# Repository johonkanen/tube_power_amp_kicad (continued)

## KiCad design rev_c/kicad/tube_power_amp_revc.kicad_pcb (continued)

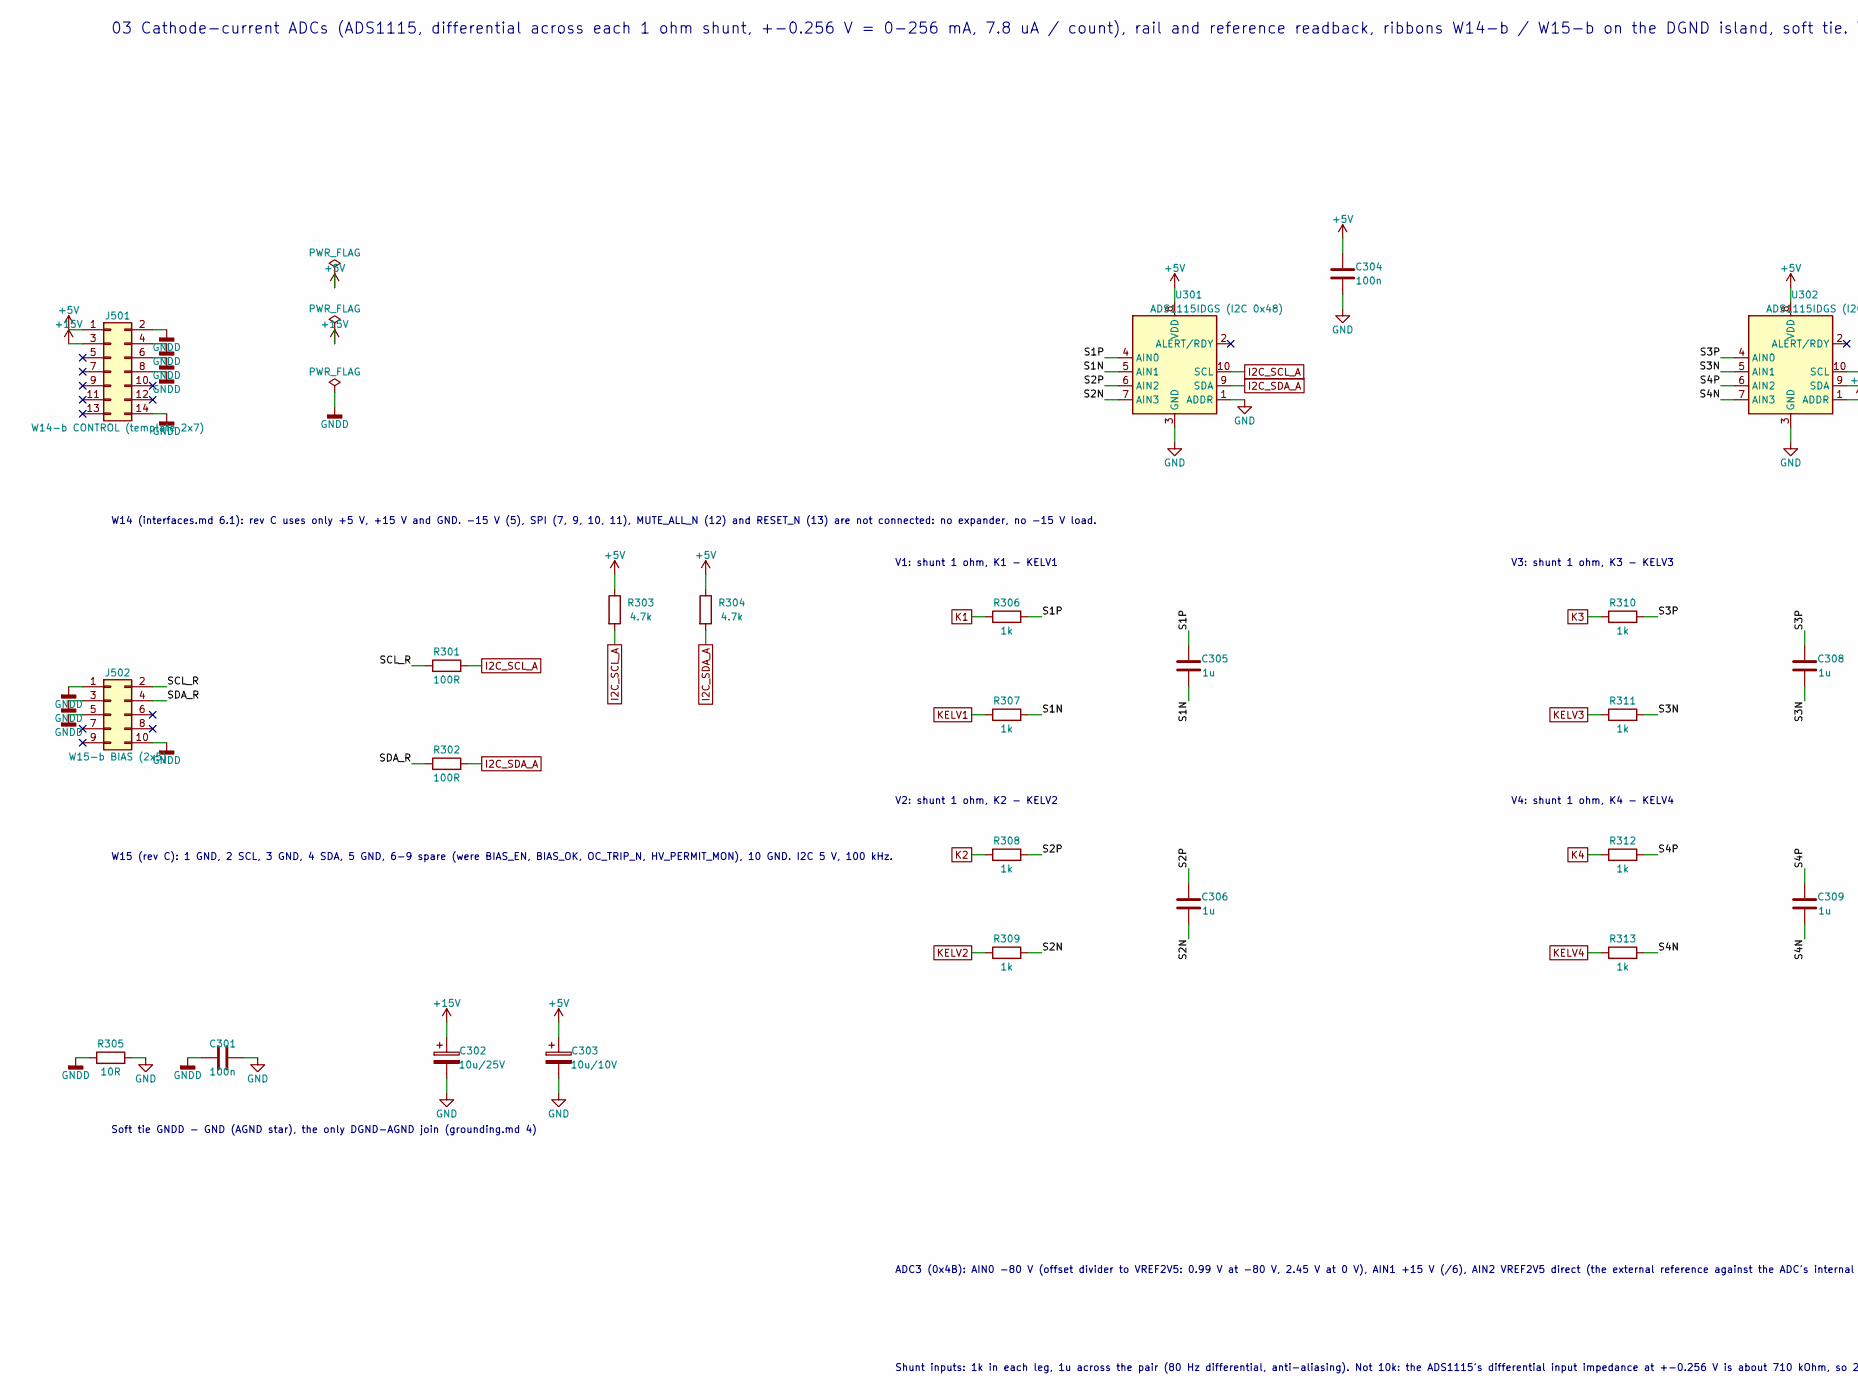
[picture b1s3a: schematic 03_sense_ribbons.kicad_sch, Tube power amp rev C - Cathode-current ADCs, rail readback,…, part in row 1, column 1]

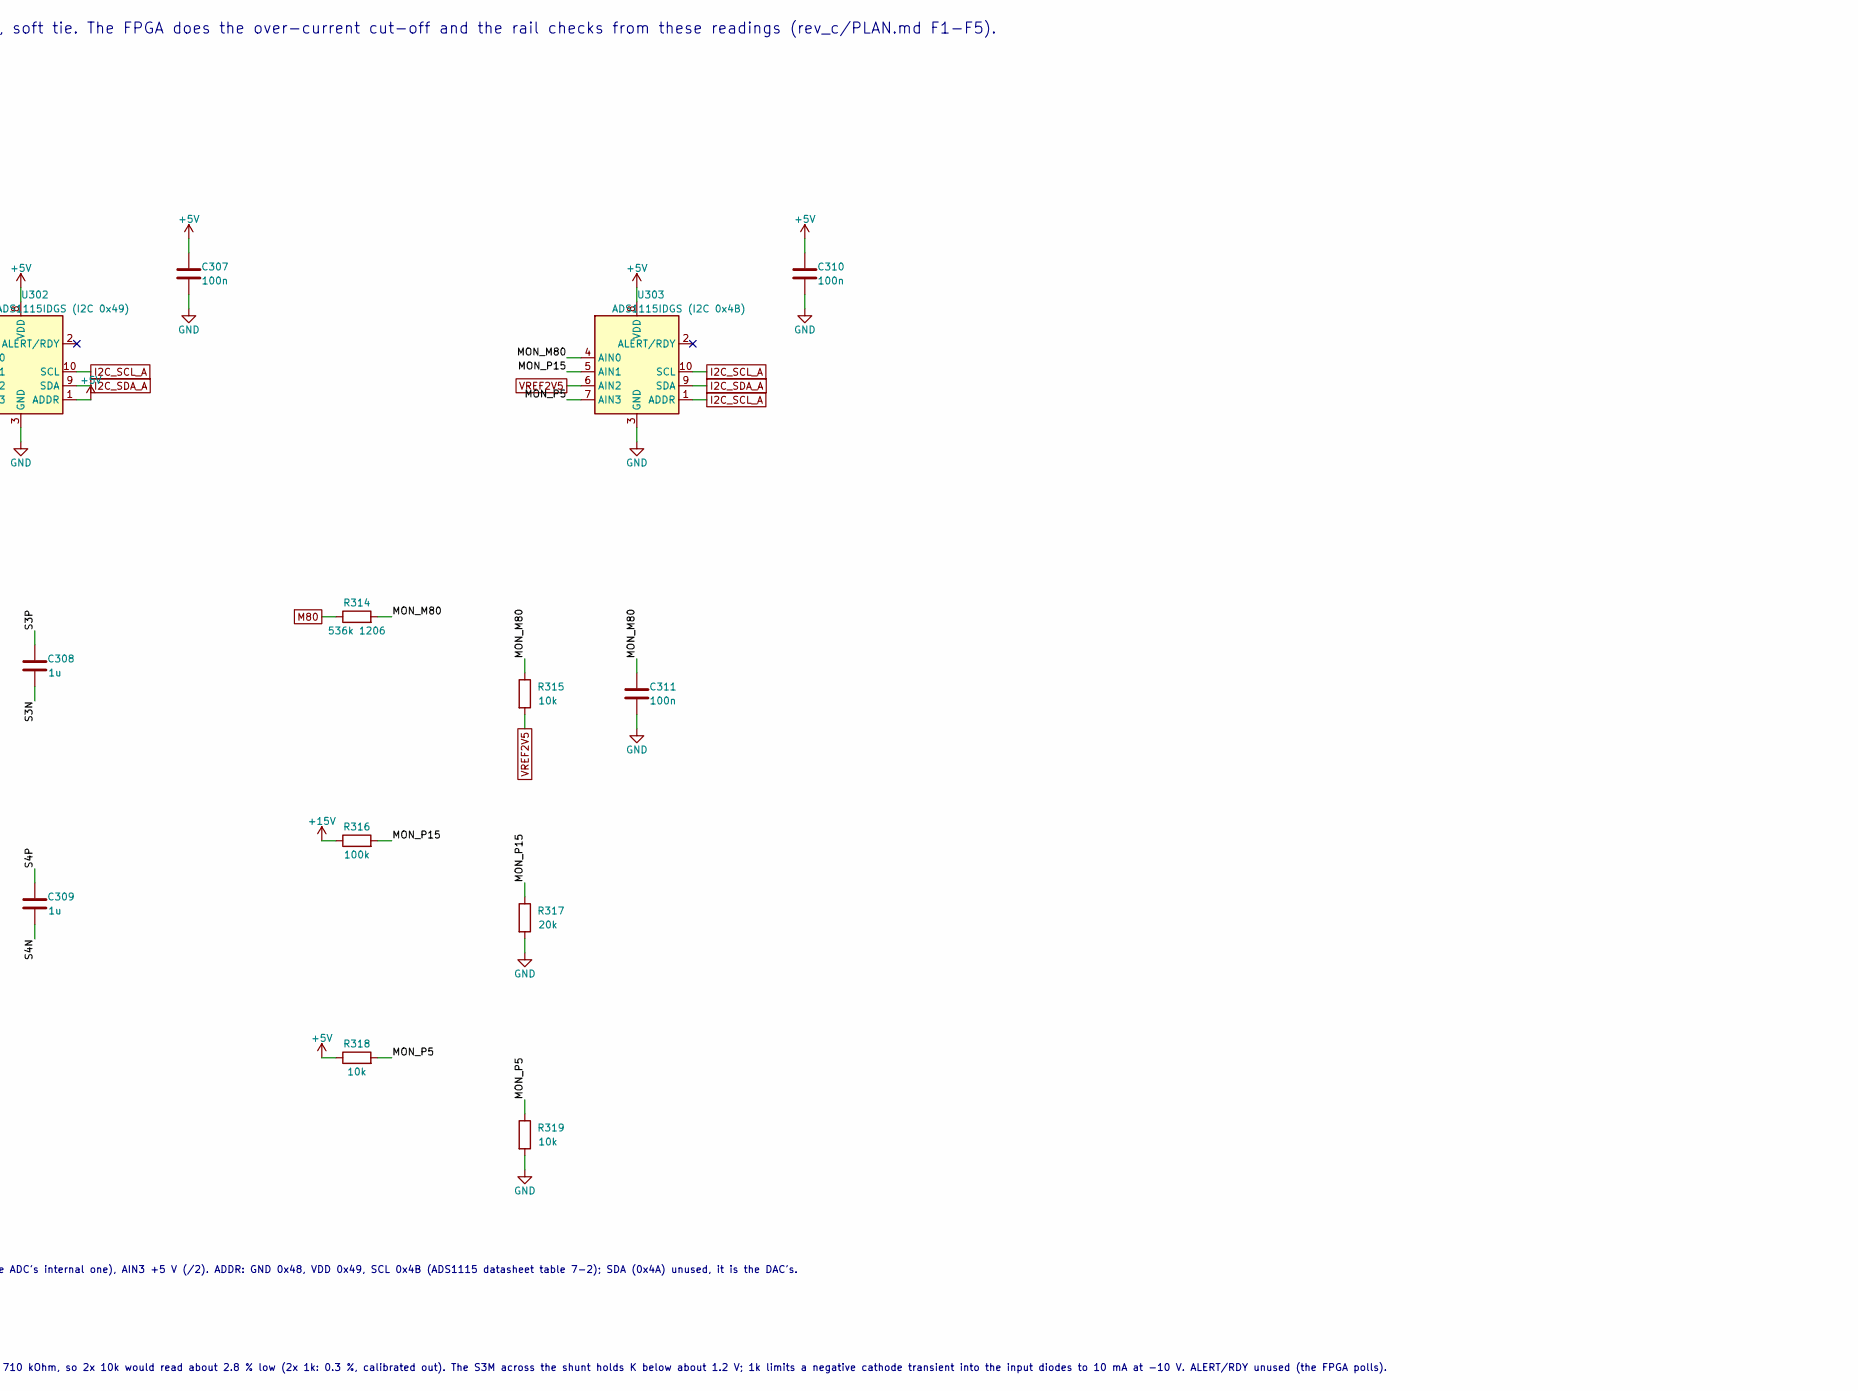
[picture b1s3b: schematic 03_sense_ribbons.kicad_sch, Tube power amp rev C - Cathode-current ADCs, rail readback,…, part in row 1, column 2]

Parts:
C301, C304, C307, C310, C311: 100n; C_0603_1608Metric
C302: 10u/25V; C_1206_3216Metric
C303: 10u/10V; C_1206_3216Metric
C305, C306, C308, C309: 1u; C_0603_1608Metric
J501: W14-b CONTROL (template 2x7); IDC-Header_2x07_P2.54mm_Vertical
J502: W15-b BIAS (2x5); IDC-Header_2x05_P2.54mm_Vertical
R301, R302: 100R; R_0603_1608Metric
R303, R304: 4.7k; R_0603_1608Metric
R305: 10R; R_0603_1608Metric
R306, R307, R308, R309, R310, R311, R312, R313: 1k; R_0603_1608Metric
R314: 536k 1206; R_1206_3216Metric
R315, R318, R319: 10k; R_0603_1608Metric
R316: 100k; R_0603_1608Metric
R317: 20k; R_0603_1608Metric
U301: ADS1115IDGS (I2C 0x48); MSOP-10_3x3mm_P0.5mm
U302: ADS1115IDGS (I2C 0x49); MSOP-10_3x3mm_P0.5mm
U303: ADS1115IDGS (I2C 0x4B); MSOP-10_3x3mm_P0.5mm

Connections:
+5V: C303.1, C304.1, C307.1, C310.1, J501.1, R303.1, R304.1, R318.1, U301.8 (VDD), U302.1 (ADDR), U302.8 (VDD), U303.8 (VDD); also elsewhere on the board
+15V: C302.1, J501.3, R316.1; also elsewhere on the board
/03 Cathode-current ADCs, rail readback, ribbons, DGND island/MON_M80: C311.1, R314.2, R315.1, U303.4 (AIN0)
/03 Cathode-current ADCs, rail readback, ribbons, DGND island/MON_P5: R318.2, R319.1, U303.7 (AIN3)
/03 Cathode-current ADCs, rail readback, ribbons, DGND island/MON_P15: R316.2, R317.1, U303.5 (AIN1)
/03 Cathode-current ADCs, rail readback, ribbons, DGND island/S1N: C305.2, R307.2, U301.5 (AIN1)
/03 Cathode-current ADCs, rail readback, ribbons, DGND island/S1P: C305.1, R306.2, U301.4 (AIN0)
/03 Cathode-current ADCs, rail readback, ribbons, DGND island/S2N: C306.2, R309.2, U301.7 (AIN3)
/03 Cathode-current ADCs, rail readback, ribbons, DGND island/S2P: C306.1, R308.2, U301.6 (AIN2)
/03 Cathode-current ADCs, rail readback, ribbons, DGND island/S3N: C308.2, R311.2, U302.5 (AIN1)
/03 Cathode-current ADCs, rail readback, ribbons, DGND island/S3P: C308.1, R310.2, U302.4 (AIN0)
/03 Cathode-current ADCs, rail readback, ribbons, DGND island/S4N: C309.2, R313.2, U302.7 (AIN3)
/03 Cathode-current ADCs, rail readback, ribbons, DGND island/S4P: C309.1, R312.2, U302.6 (AIN2)
/03 Cathode-current ADCs, rail readback, ribbons, DGND island/SCL_R: J502.2, R301.1
/03 Cathode-current ADCs, rail readback, ribbons, DGND island/SDA_R: J502.4, R302.1
GND: C301.2, C302.2, C303.2, C304.2, C307.2, C310.2, C311.2, R305.2, R317.2, R319.2, U301.1 (ADDR), U301.3 (GND), U302.3 (GND), U303.3 (GND); also elsewhere on the board
GNDD: C301.1, J501.2, J501.4, J501.6, J501.8, J501.14, J502.1, J502.3, J502.5, J502.10, R305.1; also elsewhere on the board
I2C_SCL_A: R301.2, R303.2, U301.10 (SCL), U302.10 (SCL), U303.1 (ADDR), U303.10 (SCL); also elsewhere on the board
I2C_SDA_A: R302.2, R304.2, U301.9 (SDA), U302.9 (SDA), U303.9 (SDA); also elsewhere on the board
K1: R306.1; also elsewhere on the board
K2: R308.1; also elsewhere on the board
K3: R310.1; also elsewhere on the board
K4: R312.1; also elsewhere on the board
KELV1: R307.1; also elsewhere on the board
KELV2: R309.1; also elsewhere on the board
KELV3: R311.1; also elsewhere on the board
KELV4: R313.1; also elsewhere on the board
M80: R314.1; also elsewhere on the board
VREF2V5: R315.2, U303.6 (AIN2); also elsewhere on the board

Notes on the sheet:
03 Cathode-current ADCs (ADS1115, differential across each 1 ohm shunt, +-0.256 V = 0-256 mA, 7.8 uA / count), rail and reference readback, ribbons W14-b / W15-b on the DGND island, soft tie. The FPGA does the over-current cut-off and the rail checks from these readings (rev_c/PLAN.md F1-F5).
W14 (interfaces.md 6.1): rev C uses only +5 V, +15 V and GND. -15 V (5), SPI (7, 9, 10, 11), MUTE_ALL_N (12) and RESET_N (13) are not connected: no expander, no -15 V load.
W15 (rev C): 1 GND, 2 SCL, 3 GND, 4 SDA, 5 GND, 6-9 spare (were BIAS_EN, BIAS_OK, OC_TRIP_N, HV_PERMIT_MON), 10 GND. I2C 5 V, 100 kHz.
Soft tie GNDD - GND (AGND star), the only DGND-AGND join (grounding.md 4)
V1: shunt 1 ohm, K1 - KELV1
V2: shunt 1 ohm, K2 - KELV2
V3: shunt 1 ohm, K3 - KELV3
V4: shunt 1 ohm, K4 - KELV4
ADC3 (0x4B): AIN0 -80 V (offset divider to VREF2V5: 0.99 V at -80 V, 2.45 V at 0 V), AIN1 +15 V (/6), AIN2 VREF2V5 direct (the external reference against the ADC's internal one), AIN3 +5 V (/2). ADDR: GND 0x48, VDD 0x49, SCL 0x4B (ADS1115 datasheet table 7-2); SDA (0x4A) unused, it is the DAC's.
Shunt inputs: 1k in each leg, 1u across the pair (80 Hz differential, anti-aliasing). Not 10k: the ADS1115's differential input impedance at +-0.256 V is about 710 kOhm, so 2x 10k would read about 2.8 % low (2x 1k: 0.3 %, calibrated out). The S3M across the shunt holds K below about 1.2 V; 1k limit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

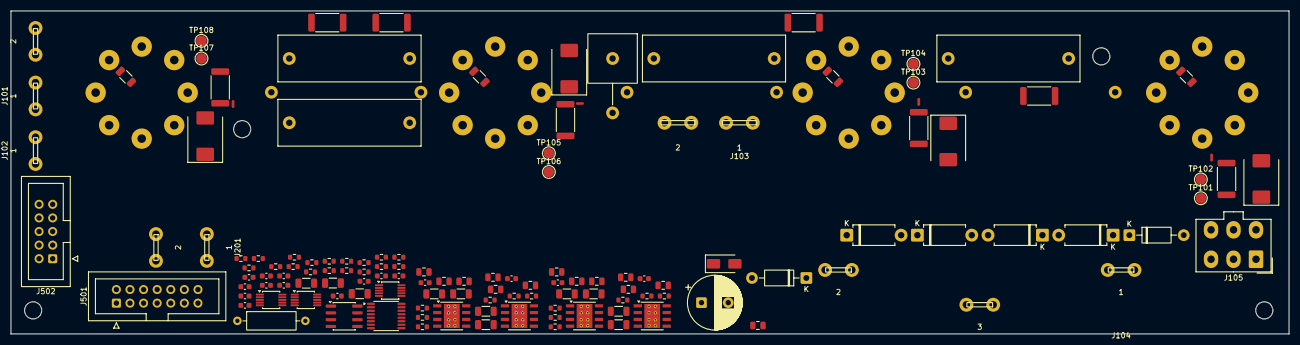
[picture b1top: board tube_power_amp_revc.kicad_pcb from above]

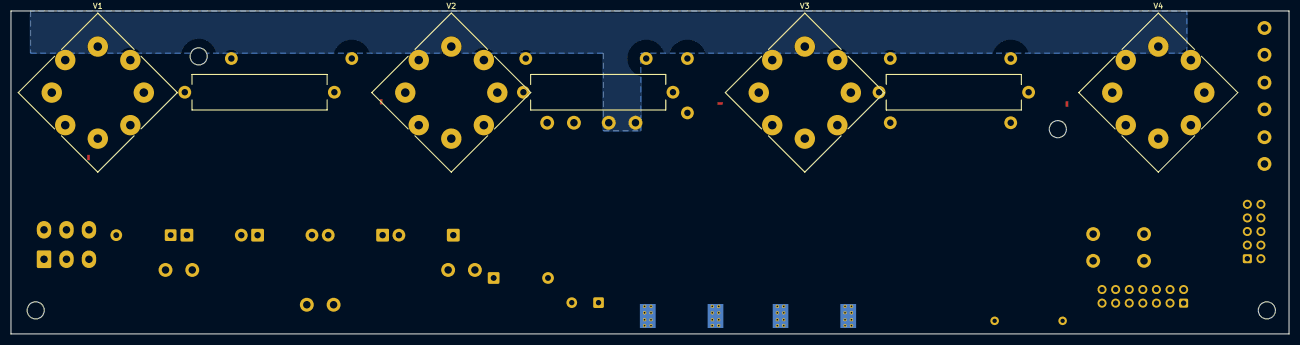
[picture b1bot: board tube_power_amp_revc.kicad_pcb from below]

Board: 4 copper layers, 238.8 x 60.3 mm, 140 parts (7 on the bottom side), 72 nets.

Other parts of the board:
H1, H2, H3, H4: M3 standoff 15 mm

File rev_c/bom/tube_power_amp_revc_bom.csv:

refs,qty,value,footprint,candidate part,note
C101 C102 C103 C104,4,220n/630V MKP,Capacitor_THT:C_Rect_L26.5mm_W8.5mm_P22.50mm_MKS4,"220n 630 V MKP, P 22.5 mm (WIMA MKP4 26.5 x 7 / Kemet R76 class)",body width <= 8.5 mm (layout)
C201,1,100u/100V 105C,Capacitor_THT:CP_Radial_D10.0mm_P5.00mm,"UPW2A101MPD (Nichicon, 105 C)",
C202 C209 C213 C217 C221,5,100n/100V,Capacitor_SMD:C_0805_2012Metric,100n 100 V X7R / X7S 0805 (GRM21BC72A105 class for 1 uF),
C203 C204 C305 C306 C308 C309,6,1u,Capacitor_SMD:C_0603_1608Metric,1u 50 V X7R 0603,
C205 C208 C212 C216 C220 C301 C304 C307 C310 C311,10,100n,Capacitor_SMD:C_0603_1608Metric,100n 50 V X7R 0603,
C206 C210 C214 C218,4,330n,Capacitor_SMD:C_0805_2012Metric,330n 50 V X7R 0805 (C0G 1206 preferred),
C207 C211 C215 C219,4,1u/100V,Capacitor_SMD:C_0805_2012Metric,1u 100 V X7R / X7S 0805 (GRM21BC72A105 class for 1 uF),
C302,1,10u/25V,Capacitor_SMD:C_1206_3216Metric,10u/25V X7R 1206,
C303,1,10u/10V,Capacitor_SMD:C_1206_3216Metric,10u/10V X7R 1206,
D101 D104,2,"RGP02-20E (2 kV, plate diode)",Diode_THT:D_DO-41_SOD81_P10.16mm_Horizontal,"RGP02-20E-E3/54 (Vishay, 2 kV, 0.5 A, 300 ns)",
D102 D103 D105 D106,4,"P6KE350CA (TVS, bidirectional)",Diode_THT:D_DO-15_P10.16mm_Horizontal,"P6KE350CA (Littelfuse; VBR 332-368 V, VC 482 V at 1.24 A)",
D107 D108 D109 D110,4,S3M (3 A),Diode_SMD:D_SMC,S3M-E3/57T (Vishay),
D201,1,S1G (reverse clamp),Diode_SMD:D_SMA,S1G (1N4004 class),
J101,1,W04-b V_ANODE / GND_PWR (4.8 mm tabs),tube_power_amp_revc:BladeTab_4.8mm_x2_P10.20mm_Inline,"2x PCB blade tab 4.8 mm (0.187 in), 2 legs on 5.00 mm, 1.4 mm holes (interfaces.md 4.1); order code to confirm",fully insulated receptacles; in line on 10.2 mm
J102,1,W05-b V_SCREEN (4.8 mm tab),tube_power_amp_revc:BladeTab_4.8mm_x1,"1x PCB blade tab 4.8 mm (0.187 in), 2 legs on 5.00 mm, 1.4 mm holes (interfaces.md 4.1); order code to confirm",fully insulated receptacle
J103,1,W06-b HEATER (6.3 mm tabs),tube_power_amp_revc:BladeTab_6.3mm_x2_P11.50mm,"2x PCB blade tab 6.3 mm (0.250 in), 2 legs on 5.00 mm, 1.4 mm holes (interfaces.md 4.1); order code to confirm",6.4 A; tabs on 11.5 mm
J104,1,W11-a OT_A / OT_B / OT_CT (4.8 mm tabs),tube_power_amp_revc:BladeTab_4.8mm_x3_OT,"3x PCB blade tab 4.8 mm (0.187 in), 2 legs on 5.00 mm, 1.4 mm holes (interfaces.md 4.1); order code to confirm","OT_A / OT_CT / OT_B at 0 / 26.4 / 52.8 mm, OT_CT 6.5 mm forward"
J105,1,"W24-b DRIVE (Mini-Fit Jr 2x3, 600 V; 280-390 V DC on pins 2 / 4)",Connector_Molex:Molex_Mini-Fit_Jr_5566-06A_2x03_P4.20mm_Vertical,Molex 39-28-1063 class (Mini-Fit Jr 5566-06A; order code to confirm),"600 V AC/DC; housing 39-01-2060, terminals 39-00-0039; circuit 6 N/C"
J201,1,W09-b -80V / BIAS_RTN (4.8 mm tabs),tube_power_amp_revc:BladeTab_4.8mm_x2_P9.50mm,"2x PCB blade tab 4.8 mm (0.187 in), 2 legs on 5.00 mm, 1.4 mm holes (interfaces.md 4.1); order code to confirm",fully insulated receptacles
J501,1,W14-b CONTROL (template 2x7),Connector_IDC:IDC-Header_2x07_P2.54mm_Vertical,61201421621 (Wurth),"shrouded, keyed"
J502,1,W15-b BIAS (2x5),Connector_IDC:IDC-Header_2x05_P2.54mm_Vertical,61201021621 (Wurth),"shrouded, keyed"
N101 N102 N103 N104,4,Kelvin at shunt pad,NetTie:NetTie-2_SMD_Pad0.5mm,,Kelvin tap at the shunt pad
R101 R105 R109 R113,4,91k,Resistor_SMD:R_2512_6332Metric,"91k 1 % 2512 high-voltage thick film, >= 500 V working (KOA HV732H / Vishay CRHV class)",grid leak; -240 V blocking transient across it (layout 2026-11-24: SMD on the B side)
R102 R106 R110 R114,4,5.6k,Resistor_SMD:R_1206_3216Metric,5.6k 1 % 1206 (200 V),"grid stopper inside the socket's pin circle, at pin 5 (layout)"
R103 R107 R115,3,1k 5W flameproof,Resistor_THT:R_Axial_Power_L25.0mm_W6.4mm_P27.94mm,"1k 5 W flameproof metal oxide (25 x 6.4 mm, as rev A)","layout 2026-11-24: mounted lying on the B (plate) side, body raised 2 mm, hand-soldered"
R104 R108 R112 R116,4,1R 1W,Resistor_SMD:R_2512_6332Metric,1R 1 W 1 % 50 ppm/K metal strip (2512),
R111,1,1k 5W flameproof,tube_power_amp_revc:R_Axial_Power_L25.0mm_W9.0mm_P10.16mm_Vertical_Tight,"1k 5 W flameproof metal oxide, standing",V3's screen resistor stands on F in the V2-V3 gap (no room for a lying one)
R201,1,10R 1W fusible wirewound,Resistor_THT:R_Axial_DIN0309_L9.0mm_D3.2mm_P12.70mm_Horizontal,CRF251-4 / CRF110 10R (Yageo Vitrohm),"fusible wirewound; inrush of C201 (8 A peak, 0.32 J) to confirm"
R202 R207 R212 R217 R315 R318 R319,7,10k,Resistor_SMD:R_0603_1608Metric,10k 1 % 0603,
R203 R208 R213 R218,4,115k,Resistor_SMD:R_0603_1608Metric,115k 1 % 0603,
R204 R209 R214 R219,4,10k 0.1%,Resistor_SMD:R_1206_3216Metric,10k 0.1 % 25 ppm/K thin film 1206,
R205 R210 R215 R220,4,280k 0.1%,Resistor_SMD:R_1206_3216Metric,280k 0.1 % 25 ppm/K thin film 1206,
R206 R211 R216 R221 R306 R307 R308 R309 R310 R311 R312 R313,12,1k,Resistor_SMD:R_0603_1608Metric,1k 1 % 0603,
R301 R302,2,100R,Resistor_SMD:R_0603_1608Metric,100R 1 % 0603,
R303 R304,2,4.7k,Resistor_SMD:R_0603_1608Metric,4.7k 1 % 0603,
R305,1,10R,Resistor_SMD:R_0603_1608Metric,10R 1 % 0603,
R314,1,536k 1206,Resistor_SMD:R_1206_3216Metric,536k 1206 (200 V),up to 80 V across it
R316,1,100k,Resistor_SMD:R_0603_1608Metric,100k 1 % 0603,
R317,1,20k,Resistor_SMD:R_0603_1608Metric,20k 1 % 0603,
TP101,1,K1 (1 mV/mA),TestPoint:TestPoint_Pad_D2.0mm,,"cathode test pad, probed from below"
TP102,1,K1 GND,TestPoint:TestPoint_Pad_D2.0mm,,"cathode test pad, probed from below"
TP103,1,K2 (1 mV/mA),TestPoint:TestPoint_Pad_D2.0mm,,"cathode test pad, probed from below"
TP104,1,K2 GND,TestPoint:TestPoint_Pad_D2.0mm,,"cathode test pad, probed from below"
TP105,1,K3 (1 mV/mA),TestPoint:TestPoint_Pad_D2.0mm,,"cathode test pad, probed from below"
TP106,1,K3 GND,TestPoint:TestPoint_Pad_D2.0mm,,"cathode test pad, probed from below"
TP107,1,K4 (1 mV/mA),TestPoint:TestPoint_Pad_D2.0mm,,"cathode test pad, probed from below"
TP108,1,K4 GND,TestPoint:TestPoint_Pad_D2.0mm,,"cathode test pad, probed from below"
U201,1,"ADR4525 (2.5 V, 0.02 %, 2 ppm/K)",Package_SO:SOIC-8_3.9x4.9mm_P1.27mm,ADR4525BRZ (ADI),
U202,1,"DAC7578SPW (12-bit x8, I2C 0x4A)",Package_SO:TSSOP-16_4.4x5mm_P0.65mm,DAC7578SPW (TI),TSSOP: power-on reset to zero scale (TI)
U203 U204 U205 U206,4,OPA462DDA (180 V),Package_SO:TI_SO-PowerPAD-8_ThermalVias,"OPA462DDAR (TI, 180 V)",PowerPAD = V- (-80 V): copper area for 0.35 W; confirm the pad against DDA0008J
U301,1,ADS1115IDGS (I2C 0x48),Package_SO:MSOP-10_3x3mm_P0.5mm,ADS1115IDGSR (TI),VSSOP-10 (DGS)
U302,1,ADS1115IDGS (I2C 0x49),Package_SO:MSOP-10_3x3mm_P0.5mm,ADS1115IDGSR (TI),VSSOP-10 (DGS)
U303,1,ADS1115IDGS (I2C 0x4B),Package_SO:MSOP-10_3x3mm_P0.5mm,ADS1115IDGSR (TI),VSSOP-10 (DGS)
V1 V2 V3 V4,4,EL34 / 6L6GC / KT88 / 6550 (octal),tube_power_amp_revc:Valve_Octal_Belton_PCD17.20mm,Belton octal PCB socket (as rev A),"solder side, as built"

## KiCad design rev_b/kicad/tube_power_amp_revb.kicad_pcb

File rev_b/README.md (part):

# Power amp rev B: schematic (third pass)

The next power amp board (4 octal output tubes, per-tube cold-by-default bias, cathode-current
measurement, over-current trip, hardware HV inhibit), drawn from the project's own documents and
simulations in [tube_amplifier_kicad](https://github.com/johonkanen/tube_amplifier_kicad):
`docs/bias_supply.md` + `sim/bias_supply` (bias supply, sense chain, trip), `docs/interfaces.md`
IF-1.1 (connectors, ribbons 6.1 / 6.3, map 7.3, safety lines 8), `docs/grounding.md`,
`sim/power_stage` (1k screen resistors, grid stoppers, bias range), SPECIFICATION.md PA-1..PA-6,
SAFE-1..SAFE-6, PS-2. Rev A (the 2010 `OUTPUT` board) at the repo root is frozen and not touched;
`rev_b/` is its own p2k board root (`p2k_config.py`, PROJECT `tube_power_amp_revb`).

Scope of this pass (2026-11-21): initial schematic, interface viability check, what has been
missed. **No layout, no footprints yet.** The check results, missed items, missing simulations and
missing requirements are in [STATUS.md](STATUS.md).

## Layout, first pass (2026-11-24)

Placed and HV-routed, low-voltage routing open (238 unconnected): see [STATUS.md](STATUS.md) "Layout, first
pass". Build: `rev_b/tools/layout/route_chain.sh` (placement `make_pcb.py` from `placement.py`, scripted HV
copper `hv_copper.py`, KiCadRoutingTools steps per `rev_b/routing.json`, pours `pours.py`); checks
`rev_b/tools/layout/check.sh`; renders `rev_b/tools/layout/render.sh`. Interface sketch:
`python3 rev_b/tools/layout_sketch.py`.

## Third pass (2026-11-23)

Decisions of 2026-11-23 drawn; details and checks in [STATUS.md](STATUS.md) "Third pass".
- **Grid leak 91k, coupling cap 220 nF / 630 V film, all four types.** Grid circuit 98 kΩ.
  **6550 deviation:** 98 kΩ is about twice the 6550's 50 kΩ fixed-bias rating (Tung-Sol); accepted by
  the user, covered by the cold-default bias, the per-tube firmware current loop and the 220 mA
  hardware over-current trip. (The "Grid circuit resistance" table below still applies; the options
  discussed there are closed.)
- **Open-load protection fitted:** RGP02-20E (2 kV) from GND to each plate; 2x P6KE350CA from each
  plate to the centre tap. Off with a load (≤ 631 V across a ≥ 664 V string), plates held at
  1.10-1.24 kV when the speaker is pulled, ≤ 6.9 mJ per event.
- **W24 = Molex Mini-Fit Jr 2x3** (39-28-1063 class), circuits 1-5 as before, 6 N/C.
- **V_ANODE:** 0.48-0.60 A average at sine overdrive, up to 0.66 A at square-wave overdrive (KT88);
  copper and tabs sized for the 2.0 A trip.

### Layout notes (added in the third pass)

- **1.25 kV nets** (OT_A, OT_B, CL_A, CL_B): ≥ 6.3 mm creepage and clearance to everything else and to
  each other (IPC-2221B B2, 0.005 mm/V); slots where needed; clamps near J104.
- **V_ANODE / OT copper:** sized for 2.0 A continuous.
- **Rear edge, x 280-322:** the rear I/O main board stands 7 mm behind this outline there (its SMD
  parts and solder joints face this board). Nothing of this board may overhang its outline there:
  no part body, tab or receptacle past the rear edge in that span.
- **Right end:** the HV supplies board's new arm is at x 525-560, y 127-200, 5.9 mm from this board's
  right end (x 519): no overhang at the right end either; the tabs facing it (V_ANODE, V_SCREEN,
  -80 V, heaters, OT) need their insulated receptacles and lead bend within the 5.9 mm gap, or enter
  from below.

## Second pass (2026-11-23)

Brought into line with interfaces.md **IF-1.2** and the bias decisions of 2026-11-22
(bias_supply.md "Corrections 2026-11-22" / "Proposed wording", review 7.1). Interface check, open
items and next steps: [STATUS.md](STATUS.md) "Second pass". Footprints are assigned on every part
(`lib/footprint_map.csv`) and a first BOM is in [bom/tube_power_amp_revb_bom.csv](bom/tube_power_amp_revb_bom.csv).

**ERC (KiCad 10.0.7): 0 errors, 1 warning** (the same as the first pass: ADS7828 REF on the ADR4525
output, intended). **326 parts** (units counted once; 157 R, 77 C, 31 Q, 28 D, 16 U, 9 J, 4 net ties,
4 tubes), 97 BOM lines, 5 sheets.

### What changed, decision by decision

| # | Decision / request | What is drawn now | Why / check |
|---|---|---|---|
| 1 | Sense filter: two real poles, 47k / 220 nF twice (5.3 / 40 Hz) | Per tube a second 220n (A2n to KELVn), the old 330n now 220n (sheet 04). Gain set to exactly 10.0: 9.09k / **1.01k** 0.1 % (9.09k / 1k was 10.09, +0.9 %) | Master `run_sense_filter.py` variant `two_real_220` is this circuit: 25 ms to 400 mA, 45-50 ms mirror short, 13 mA pp at 82 Hz |
| 2 | 72 V string (2x 36 V) with 3.3k | 2x **BZT52H-B36** (SOD123F, ±2 %), 3.3k 1206 | TC checked against the Nexperia datasheet: SZ 30.4 / 33.0 / 37.4 mV/K at 2 mA, the figures the master's tolerance run used, so **no re-run of the corner check is needed**. New: self-heating. SOT-23 (BZX84) is 500 K/W: 2.4 mA x 36 V = 86 mW = +43 K per zener, +2.8 V on the string. BZT52H on 1 cm² cathode copper is 150 K/W: +12 K, about +0.8 V on the string at -80 V. That only makes VNC more negative (colder; the weakest-VNC corner, cold board at -78 V, carries the least current), and in the regulation corner (70 °C, +2 %, -78 V, 0.4 mA) it adds 2 K / 0.13 V, so the string stays in regulation. Choose SOD123F with the copper, not SOT-23 |
| 3 | BIAS_OK from two hardware monitors + "+15 V present", independent of BIAS_EN | Sheet 02, one LM2901B (U202): VNC monitor (169k + 234k / 29.4k 0.1 %, 3.57M hysteresis), rail monitor (271k / 16.9k 0.1 %, 7.32M), **+15 V monitor** (trip 13.0 V against VREF2V5, so it doesn't lean on VREF10), diode-OR into MON_FAULT (clamps every channel), fourth unit makes BIAS_OK_PRE (pulled up from +15 V) → 74LVC2G17 Schmitt → BIAS_OK_A. LM4040**A**10 (0.1 %) fed by 1.0k (was 2.2k: VREF10 now regulates down to 11.5 V of +15 V); low-leakage BAS416 clamps on the monitor nodes | `sim/bias_supply/monitors.py` → [results/monitors.md](sim/bias_supply/results/monitors.md): real circuit, 0-85 °C Monte Carlo. VNC trip -62.10 to -63.90 V, release -63.6 to -65.44 V (at 0 °C, where the weakest VNC -66.4 V sits: -65.08 V worst, 1.3 V clear); rail trip -73.95 to -76.05 V, release worst -76.57 V (1.2 V clear of the lowest rail -77.8 V); SPICE sweep of the drawn block: -62.98 / -64.51 V, -75.00 / -75.49 V, 13.00 / 13.25 V. Start-up with six rail orders and slow ramps: BIAS_OK never high while VNC, the rail or +15 V is outside its window; high 84-88 ms after the rails are good. -80 V lost with the HV on: BIAS_OK low after 28-65 ms, bias drift 0.02 V |
| 4 | Over-current 220 mA ±5 %, latched, powers up tripped; expander required | LM2901B (was LM339: 0-70 °C part), VOC 39k / 11k **0.1 %**, ADC/comparator clamp BAV199 (BAT54S leakage at 85 °C would be up to 2.5 mA of reading error through the 1k), latch ~R/D through the Schmitt (first-pass item: slow RC into a non-Schmitt 74HC74 input). Expander fitted (U501) | Worst-case threshold error **±3.4 %**: LM4040A 0.1 % + 100 ppm/K x 60 K = 0.7 %; divider 0.2 % + TCR 0.3 %; shunt 1 % + 50 ppm/K x 75 K = 1.4 %; gain 0.2 % + 0.3 %; offsets 0.3 % |
| 5 | -80 V: 25 mA, ±2 V, 10 Ω fusible, no hold-up | R201 10R 1 W fusible wirewound (CRF251-4 class), C201 100 µF kept (it is what the BIAS_OK timing assumes) | Current with the monitors and ADC dividers: **5.4 / 14.2 / 21.3 mA** (cold / typical / hot end, typical board), about 22.7 mA worst case (master 22.0 + 0.7 mA of dividers) — inside 25 mA. Open: the 8 A / 0.32 J inrush of C201 through the fusible part (datasheet gives energy 0.9 W·s but no peak-current time base) |
| 6 | BIAS_EN: ≥ 470 Ω or a buffer, re-check the pump | R230 **1k** in series with the pump capacitor, hold resistor R231 **56k** (was 100k) | monitors.md section 5: 74AHCT + 100 Ω + 100 Ω + 1k: **3.8 mA peak** (8 mA rating); release 1.2-4.5 ms; cold 123-131 ms (2N7002 Vth 1.0 V) / 76-79 ms (2.5 V) after stopping high or low, at 5, 10 and 15 kHz. With 100k the 5 V drive charged the pump higher and the cold time grew to 184-202 ms. No buffer needed |
| 7 | W24 280 V DC, up to 390 V | Coupling caps 630 V MKP on a 15 mm footprint (47n or 100n fit); grid leaks axial 0207, 350 V (blocking transients put -240 V across them) | **The KK-396 header is rated 250 V** (Molex 26-60-4050 sheet; JST VH 250 V too): it fails. TE MTA-156 (3.96 mm) is rated 600 V AC, Molex Mini-Fit Jr 600 V AC/DC. Footprint kept as a marked placeholder. STATUS proposal P1 |
| 8 | Grid leak / coupling cap OPEN; max fixed-bias grid resistance | 47n / 100k drawn, marked OPEN, footprints take 100n and 220k | See "Grid circuit resistance" below: the limit is **50 kΩ (6550, Tung-Sol)**, then 100 kΩ (6L6GC; KT88 GEC) |
| 9 | Grounding: bias, DAC, ADC on AGND; DGND island; ~100 Ω crossings | Unchanged from the first pass (it already matched): GND = AGND star at J101-2; GNDD island with J501, J502, U501, J201-2; soft tie 10 Ω ‖ 100 nF; 100 Ω on I2C, BIAS_EN, BIAS_OK, OC_TRIP_N, HV_PERMIT_MON, OC_CLR, HV_REQ | — |
| 10 | 70 °C under the plate | Every IC now rated to 125 °C except **LM4040-10 (I grade only, 85 °C)**, **ADS7828E (85 °C)** and PC817 (100 °C); electrolytics 105 °C; the zener filter capacitor is ceramic (an electrolytic's 3 µA leakage through 100k would move VNC 0.3 V) | Placement below |

### Grid circuit resistance (fixed bias), from the tube datasheets

| Tube | Fixed bias max | Cathode bias max | Source |
|---|---|---|---|
| EL34 | 500 kΩ (Philips class B; Mullard, Tung-Sol EL34B, New Sensor) | 700 kΩ | Philips 1959, Mullard 1962, Tung-Sol EL34B |
| 6L6GC | **100 kΩ** (GE, RCA, Tung-Sol) | 500 kΩ | GE ET-T1515A, RCA 8-60, Tung-Sol 1960 |
| KT88 | **100 kΩ** (GEC 1959); Gold Lion reissue 220 kΩ below 35 W, 100 kΩ above | 220 kΩ (GEC) | GEC Issue 2, Genalex 2002 draft |
| 6550 | **50 kΩ** (Tung-Sol) | 250 kΩ | tungsol.com 6550 sheet (GE 6550A not found) |

The DC grid circuit here is grid leak + 1k (bias output) + the bias source (a few Ω) + 5.6k
stopper: 107 kΩ with 100k, 227 kΩ with 220k. **The limit that sets it is 6550 at 50 kΩ**; with 6550
excluded it is 100 kΩ (6L6GC and KT88), which 100k + 6.6k already exceeds by 7 %. 220k exceeds
every type except EL34. The datasheet limit guards against runaway from grid (gas, leakage)
current with a fixed bias; here the bias is a closed firmware loop on each cathode current plus a
220 mA hardware trip, which catches a slow runaway, but that is an argument, not a rating.
Options for the user: keep ≤ 100k (and accept ~2x the 6550 rating, or drop the 6550 from the list),
or meet the 6550 too with 39k + 270n / 630 V (45.6 kΩ in all, 15 Hz like 100n / 100k), which costs
drive: two 39k per side load the PI's ~40 kΩ plate to about 20 kΩ, half the swing the PI + FX
simulations assumed. Decision with the PI + FX open-load simulation (interfaces.md 14).

### Placement and temperatures (for the layout pass)

The board hangs under the plate with the sockets on the solder side; the tubes stand above the
plate, so the board sees the 70 °C air, the hot socket pins (about 100 °C and more within 10 mm of
a power-tube socket) and the four 5 W screen resistors (up to about 1.6 W each in overdrive) below it.
- Sockets in the front strip as built; screen resistors, shunts, S3M diodes, coupling caps and grid
  parts next to their socket; the anode / screen / tab region at the end toward the HV supplies.
- **Reference end** (LM4040, the two 0.1 % monitor dividers, the zener string, ADR4525, DAC,
  ADC, the sense op amps' gain resistors): the rear edge, at the low-voltage end next to the
  ribbons, at least 40 mm from the nearest socket centre and not above or beside a screen resistor.
  Assumed **70 °C air + up to 15 K = 85 °C** (the Monte Carlo above runs at 0 / 25 / 85 °C); this is
  what the LM4040-10 and ADS7828 (85 °C parts) allow, with no margin.
- **Op amps and comparators** (OPA4197, LM2901B, 125 °C parts): in the same rear strip; assumed 85 °C.
- **300 V transistors** (MMBTA92 mirrors, MMBTA42 followers, BSP92P): between the reference end and
  the sockets, at least 25 mm from a socket; assumed **90 °C**. Leakage there is a bias error that
  the firmware loop removes; vendor data at temperature is still to check (S1).
- Measure the real board temperature (M39) before freezing the 85 °C parts.

### V_ANODE current

The board carries the whole plate current from J101 to the OT centre tap on J104 (OT_CT = V_ANODE):
**about 0.57 A average for a KT88 set at full sine overdrive** (more than the 0.5 A peak budget),
with peaks above that at the clipping edges. The board needs: V_ANODE / OT_CT copper and the 4.8 mm
tabs sized for the HV supplies' 1.0 A trip continuously (tabs are good for several A; traces 2.5 mm
in 2 oz or more). The figure to put in the budget is the HV side's question (review X35); from this
board: 0.6 A average, 1.0 A sized.

## Build

```
python3 rev_b/tools/make_lib.py          # lib/tube_power_amp_revb.kicad_sym from KiCad's stock libraries (flattened)
python3 rev_b/tools/make_project.py      # project, root sheet, empty sub-sheets
python3 rev_b/tools/make_footprints.py   # board-local footprints (octal, 5 W, blade-tab placeholders), fp-lib-table
python3 rev_b/tools/sheets/draw_all.py   # draws all five sheets, writes lib/footprint_map.csv and bom/*.csv
python3 rev_b/sim/bias_supply/monitors.py   # second pass: monitors, start-up, -80 V lost, pump -> results/monitors.md
python3 rev_b/sim/checks.py              # first pass (76 V string, old bias.py): kept for the record
cd rev_b/kicad && ../../tools/p2k/bin/kicad-cli sch erc tube_power_amp_revb.kicad_sch
```

The sheets are generated: edit `tools/sheets/draw_all.py`, not the `.kicad_sch` files, until the
draft is frozen. Drawing style is netlist-first (parts on a grid, a wire stub and a label on every
pin), exact for ERC and the netlist; a tidy layout pass comes later. The one change to a stock
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
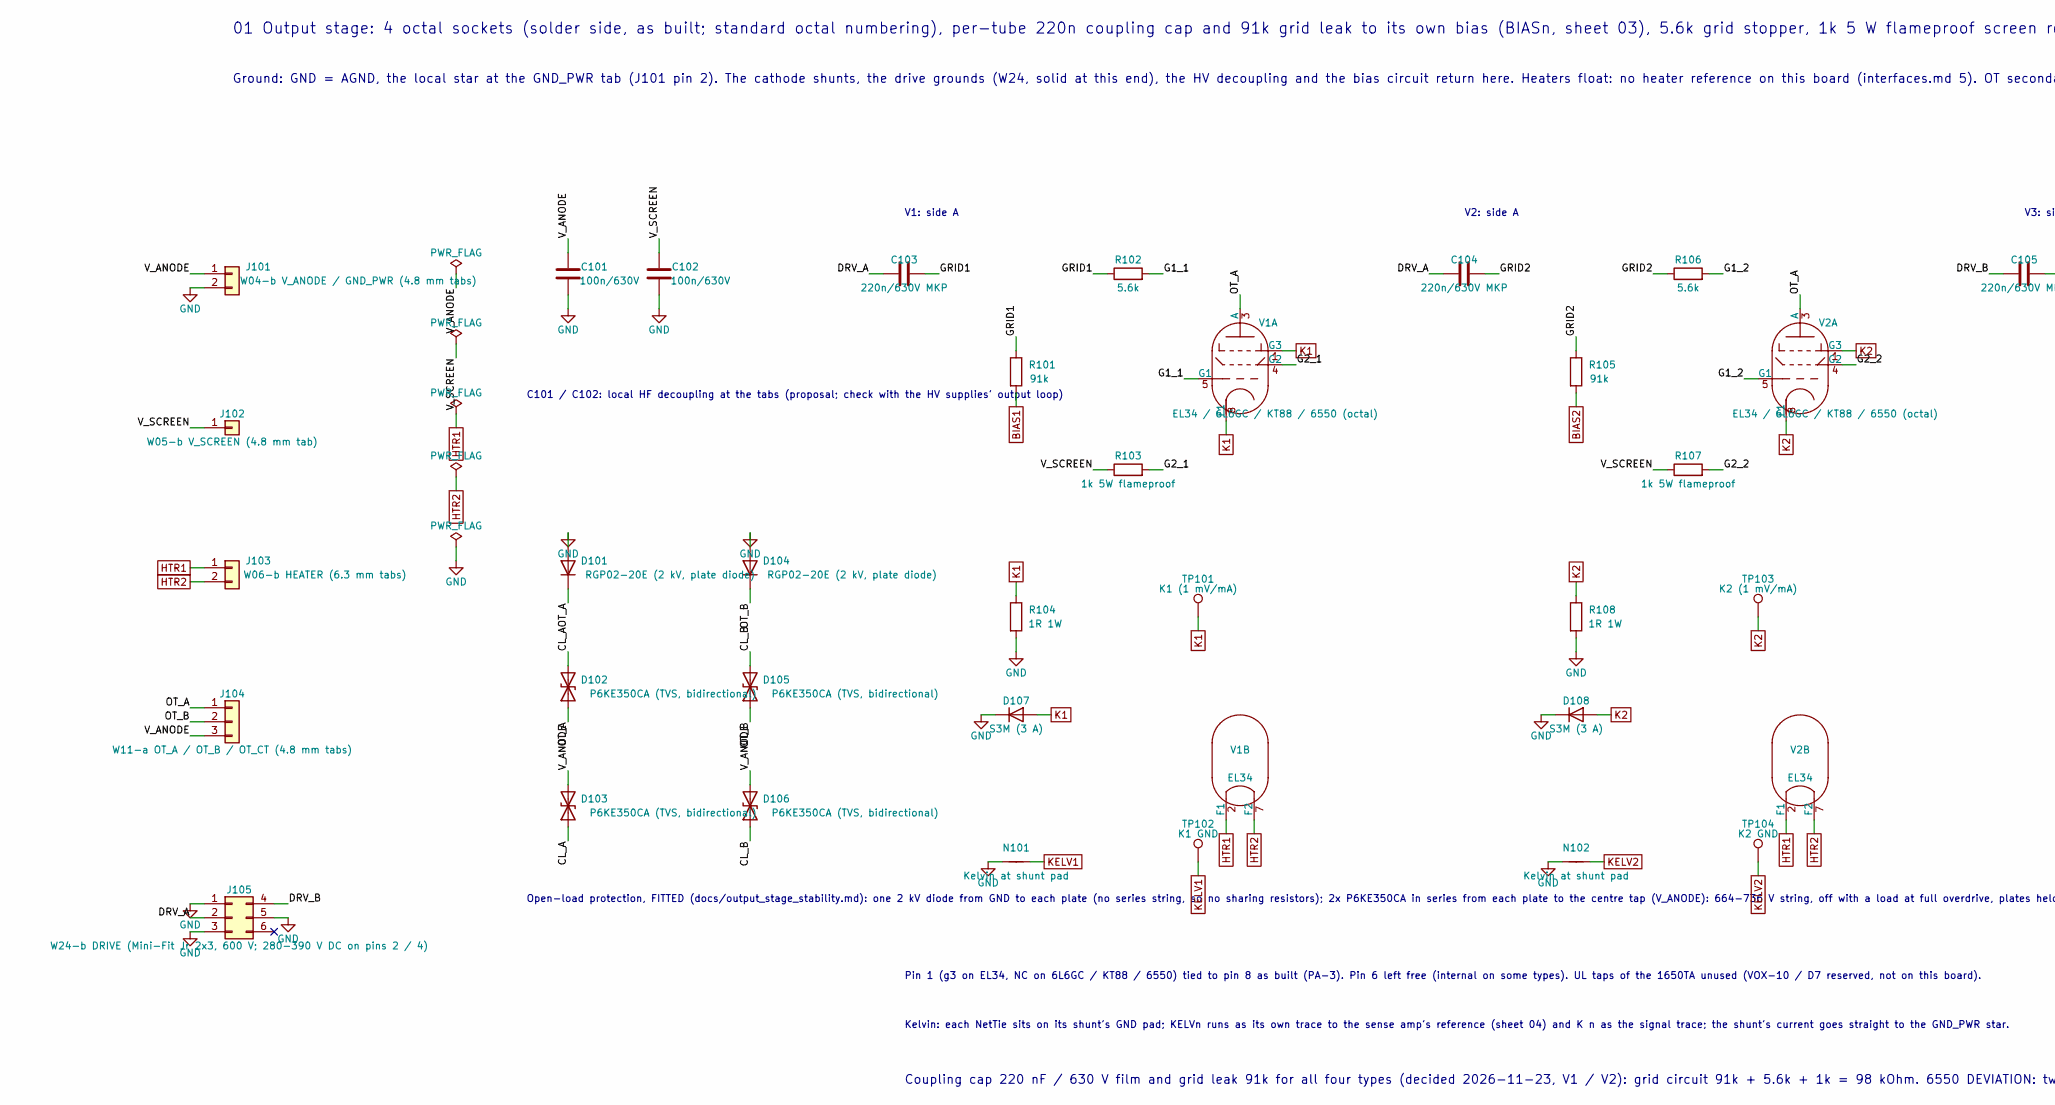
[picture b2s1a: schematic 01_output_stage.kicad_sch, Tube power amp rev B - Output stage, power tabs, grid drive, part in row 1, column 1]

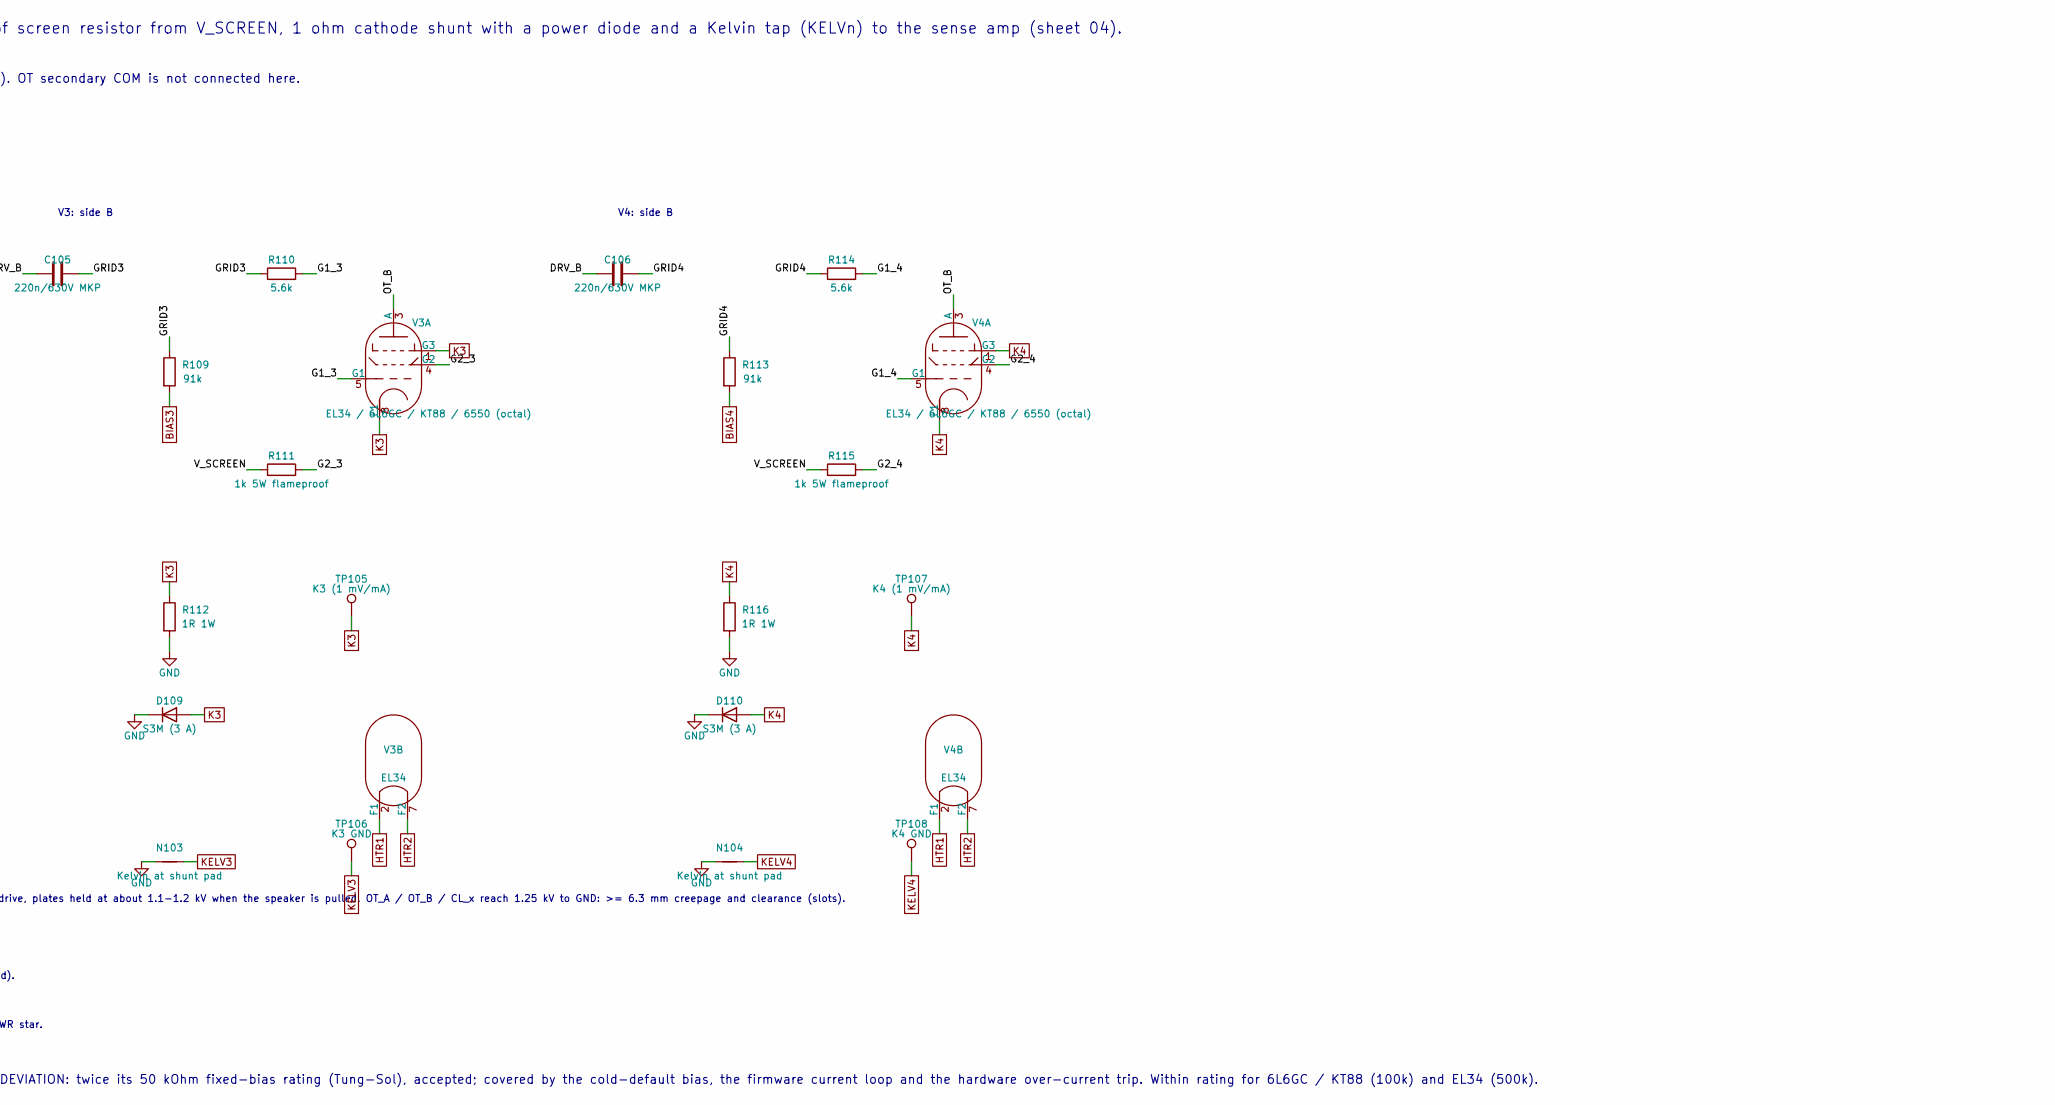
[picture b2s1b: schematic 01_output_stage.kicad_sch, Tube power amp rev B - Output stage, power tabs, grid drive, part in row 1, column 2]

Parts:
C101, C102: 100n/630V; C_1812_4532Metric
C103, C104, C105, C106: 220n/630V MKP; C_Rect_L26.5mm_W8.5mm_P22.50mm_MKS4
D101, D104: RGP02-20E (2 kV, plate diode); D_DO-41_SOD81_P10.16mm_Horizontal
D102, D103, D105, D106: P6KE350CA (TVS, bidirectional); D_DO-15_P10.16mm_Horizontal
D107, D108, D109, D110: S3M (3 A); D_SMC
J101: W04-b V_ANODE / GND_PWR (4.8 mm tabs); BladeTab_4.8mm_x2_P10.20mm_Inline
J102: W05-b V_SCREEN (4.8 mm tab); BladeTab_4.8mm_x1
J103: W06-b HEATER (6.3 mm tabs); BladeTab_6.3mm_x2_P11.50mm
J104: W11-a OT_A / OT_B / OT_CT (4.8 mm tabs); BladeTab_4.8mm_x3_OT
J105: W24-b DRIVE (Mini-Fit Jr 2x3, 600 V; 280-390 V DC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; Molex_Mini-Fit_Jr_5566-06A_2x03_P4.20mm_Vertical
N101, N102, N103, N104: Kelvin at shunt pad; NetTie-2_SMD_Pad0.5mm
R101, R105, R109, R113: 91k; R_2512_6332Metric
R102, R106, R110, R114: 5.6k; R_1206_3216Metric
R103, R107, R115: 1k 5W flameproof; R_Axial_Power_L25.0mm_W6.4mm_P27.94mm
R104, R108, R112, R116: 1R 1W; R_2512_6332Metric
R111: 1k 5W flameproof; R_Axial_Power_L25.0mm_W9.0mm_P10.16mm_Vertical_Tight
TP101: K1 (1 mV/mA); TestPoint_Pad_D2.0mm
TP102: K1 GND; TestPoint_Pad_D2.0mm
TP103: K2 (1 mV/mA); TestPoint_Pad_D2.0mm
TP104: K2 GND; TestPoint_Pad_D2.0mm
TP105: K3 (1 mV/mA); TestPoint_Pad_D2.0mm
TP106: K3 GND; TestPoint_Pad_D2.0mm
TP107: K4 (1 mV/mA); TestPoint_Pad_D2.0mm
TP108: K4 GND; TestPoint_Pad_D2.0mm
V1, V2, V3, V4: EL34 / 6L6GC / KT88 / 6550 (octal); Valve_Octal_Belton_PCD17.20mm

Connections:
/01 Output stage, power tabs, grid drive/CL_A: D102.2 (A2), D103.1 (A1)
/01 Output stage, power tabs, grid drive/CL_B: D105.2 (A2), D106.1 (A1)
/01 Output stage, power tabs, grid drive/DRV_A: C103.1, C104.1, J105.2
/01 Output stage, power tabs, grid drive/DRV_B: C105.1, C106.1, J105.4
/01 Output stage, power tabs, grid drive/G1_1: R102.2, V1.5 (G1)
/01 Output stage, power tabs, grid drive/G1_2: R106.2, V2.5 (G1)
/01 Output stage, power tabs, grid drive/G1_3: R110.2, V3.5 (G1)
/01 Output stage, power tabs, grid drive/G1_4: R114.2, V4.5 (G1)
/01 Output stage, power tabs, grid drive/G2_1: R103.2, V1.4 (G2)
/01 Output stage, power tabs, grid drive/G2_2: R107.2, V2.4 (G2)
/01 Output stage, power tabs, grid drive/G2_3: R111.2, V3.4 (G2)
/01 Output stage, power tabs, grid drive/G2_4: R115.2, V4.4 (G2)
/01 Output stage, power tabs, grid drive/GRID1: C103.2, R101.1, R102.1
/01 Output stage, power tabs, grid drive/GRID2: C104.2, R105.1, R106.1
/01 Output stage, power tabs, grid drive/GRID3: C105.2, R109.1, R110.1
/01 Output stage, power tabs, grid drive/GRID4: C106.2, R113.1, R114.1
/01 Output stage, power tabs, grid drive/OT_A: D101.1 (K), D102.1 (A1), J104.1, V1.3 (A), V2.3 (A)
/01 Output stage, power tabs, grid drive/OT_B: D104.1 (K), D105.1 (A1), J104.2, V3.3 (A), V4.3 (A)
/01 Output stage, power tabs, grid drive/V_ANODE: C101.1, D103.2 (A2), D106.2 (A2), J101.1, J104.3
/01 Output stage, power tabs, grid drive/V_SCREEN: C102.1, J102.1, R103.1, R107.1, R111.1, R115.1
BIAS1: R101.2; also elsewhere on the board
BIAS2: R105.2; also elsewhere on the board
BIAS3: R109.2; also elsewhere on the board
BIAS4: R113.2; also elsewhere on the board
GND: C101.2, C102.2, D101.2 (A), D104.2 (A), D107.1 (K), D108.1 (K), D109.1 (K), D110.1 (K), J101.2, J105.1, J105.3, J105.5, N101.1, N102.1, N103.1, N104.1, R104.2, R108.2, R112.2, R116.2; also elsewhere on the board
HTR1: J103.1, V1.2 (F1), V2.2 (F1), V3.2 (F1), V4.2 (F1); also elsewhere on the board
HTR2: J103.2, V1.7 (F2), V2.7 (F2), V3.7 (F2), V4.7 (F2); also elsewhere on the board
K1: D107.2 (A), R104.1, TP101.1, V1.1 (G3), V1.8 (F1); also elsewhere on the board
K2: D108.2 (A), R108.1, TP103.1, V2.1 (G3), V2.8 (F1); also elsewhere on the board
K3: D109.2 (A), R112.1, TP105.1, V3.1 (G3), V3.8 (F1); also elsewhere on the board
K4: D110.2 (A), R116.1, TP107.1, V4.1 (G3), V4.8 (F1); also elsewhere on the board
KELV1: N101.2, TP102.1; also elsewhere on the board
KELV2: N102.2, TP104.1; also elsewhere on the board
KELV3: N103.2, TP106.1; also elsewhere on the board
KELV4: N104.2, TP108.1; also elsewhere on the board

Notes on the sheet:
01 Output stage: 4 octal sockets (solder side, as built; standard octal numbering), per-tube 220n coupling cap and 91k grid leak to its own bias (BIASn, sheet 03), 5.6k grid stopper, 1k 5 W flameproof screen resistor from V_SCREEN, 1 ohm cathode shunt with a power diode and a Kelvin tap (KELVn) to 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
Coupling cap 220 nF / 630 V film and grid leak 91k for all four types (decided 2026-11-23, V1 / V2): grid circuit 91k + 5.6k + 1k = 98 kOhm. 6550 DEVIATION: twice its 50 kOhm fixed-bias rating (Tung-Sol), accepted; covered by the cold-default bias, the firmware current loop and the hardware over-cu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
Ground: GND = AGND, the local star at the GND_PWR tab (J101 pin 2). The cathode shunts, the drive grounds (W24, solid at this end), the HV decoupling and the bias circuit return here. Heaters float: no heater reference on this board (interfaces.md 5). OT secondary COM is not connected here.
C101 / C102: local HF decoupling at the tabs (proposal; check with the HV supplies' output loop)
Open-load protection, FITTED (docs/output_stage_stability.md): one 2 kV diode from GND to each plate (no series string, so no sharing resistors); 2x P6KE350CA in series from each plate to the centre tap (V_ANODE): 664-736 V string, off with a load at full overdrive, plates held at about 1.1-1.2 kV 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
V1: side A
V2: side A
V3: side B
V4: side B
Pin 1 (g3 on EL34, NC on 6L6GC / KT88 / 6550) tied to pin 8 as built (PA-3). Pin 6 left free (internal on some types). UL taps of the 1650TA unused (VOX-10 / D7 reserved, not on this board).
Kelvin: each NetTie sits on its shunt's GND pad; KELVn runs as its own trace to the sense amp's reference (sheet 04) and K n as the signal trace; the shunt's current goes straight to the GND_PWR star.
